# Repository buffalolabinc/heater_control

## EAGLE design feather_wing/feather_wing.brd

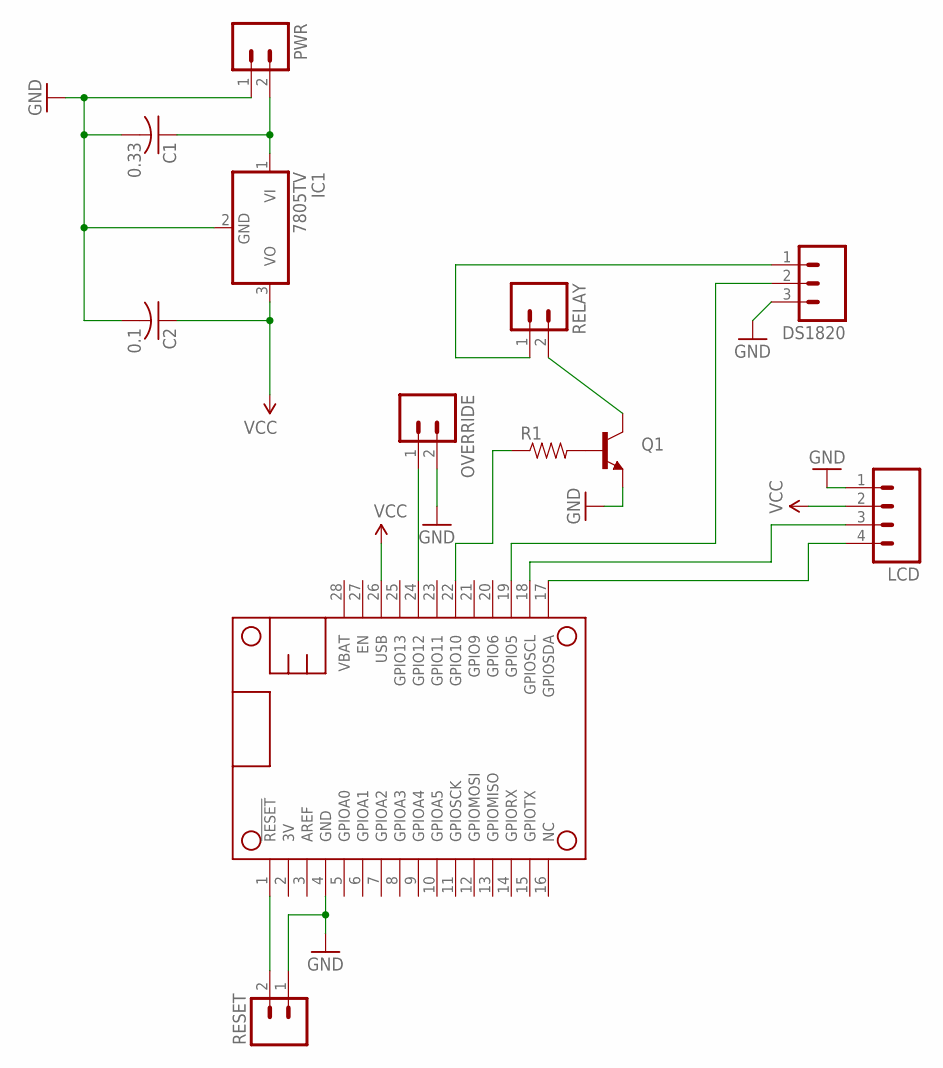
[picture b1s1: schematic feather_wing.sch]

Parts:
C1: 0.33; C025-025X050
C2: 0.1; C025-025X050
DS1820: M03SCREW; SCREWTERMINAL-3.5MM-3
IC1: 7805TV; TO220V
LCD: M04LOCK; 1X04_LOCK
MS1: FEATHERWING
OVERRIDE: M02PTH; 1X02
PWR: M023.5MM; SCREWTERMINAL-3.5MM-2
Q1: TRANSISTOR_NPNP2N2222A; TO-92
R1: RESISTORAXIAL-0.3; AXIAL-0.3
RELAY: M023.5MM; SCREWTERMINAL-3.5MM-2
RESET: M02PTH; 1X02

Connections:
GND: C1.2, C2.2, DS1820.3, IC1.2 (GND), LCD.1, MS1.4 (GND), OVERRIDE.2, PWR.1, Q1.3 (E), RESET.1
unnamed: C1.1, IC1.1 (VI), PWR.2
unnamed: DS1820.2, MS1.19 (GPIO5)
unnamed: MS1.24 (GPIO12), OVERRIDE.1
unnamed: Q1.1 (C), RELAY.2
unnamed: Q1.2 (B), R1.P$2 (2)
unnamed: MS1.22 (GPIO10), R1.P$1 (1)
unnamed: LCD.3, MS1.18 (GPIOSCL)
unnamed: LCD.4, MS1.17 (GPIOSDA)
unnamed: MS1.1 (!RESET), RESET.2
unnamed: DS1820.1, RELAY.1
VCC: C2.1, IC1.3 (VO), LCD.2, MS1.26 (USB)

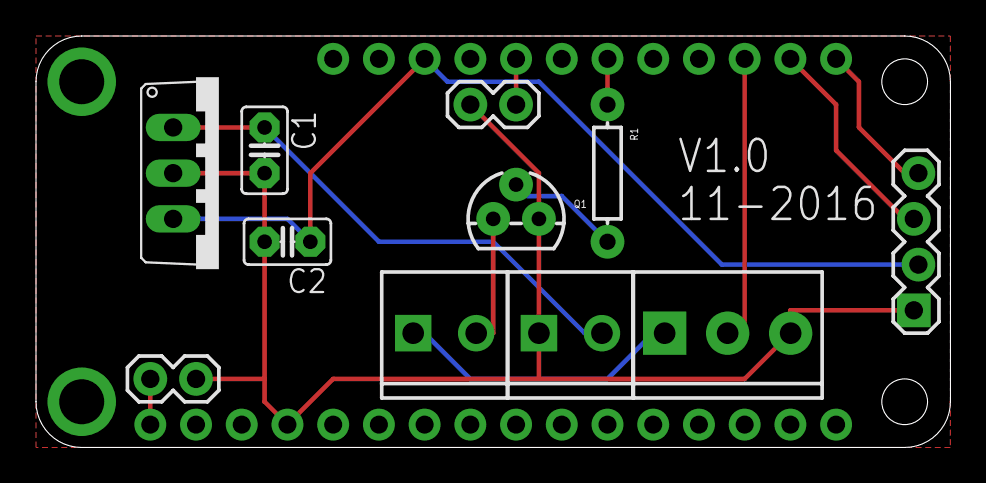
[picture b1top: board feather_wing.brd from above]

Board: 2 copper layers, 50.8 x 22.9 mm, 12 parts (0 on the bottom side), 12 nets.

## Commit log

2016-11-15 Initial check-in
    Thermostat sketch
2016-11-17 Change set points, no hang on Adafruit IO
    Changed set-points to 65 and 55.
    Will no longer block on failure to connect to Adafruit IO MQTT
2016-11-25 Take LCDDisplayTemp out of override ISR
2016-11-30 Re-do scheduler
    Change scheduler to avoid canceling timers on override.
    Also eliminate conflict between UTC and local time in CorrectDSTsettings
2016-12-01 improve scheduler and DST
2016-12-02 Daylight Savings, display, trace output changes
    Daylight savings is now done in UTC. Schedule operations are still
    local time.
    Added override indication to display.
    Removed some debug traces from temperature
    Changed MQTT trace text
2016-12-19 some debug prints
2016-12-26 Fix divide-by-zero when no sensors are attached.
2016-12-26 oops - meant to add a failsafe
    Heat won’t come on if no temp sensors are attached.
2016-12-29 Add override feed, change feed rate, debounce interrupt
    Added feed for the override state
    debounced override interrupt
    changed feed rate to be less than the MQTT keep alive interval of 5
    minutes.
2017-01-04 Add telnet settings
    MQTT settings now stored in EEPROM. Added telnet server for
    configuration
2017-01-04 move some includes to common.h
2017-01-04 Reinit MQTT after settings change
2017-01-05 Add scheduler values to telnet
    Add scheduler and setpoint values to telnet settings. Change override
    feed to setpoint feed
2017-01-05 comments
2017-01-05 fix problem with MQTT feeds
2017-01-06 Use edit buffer for changing settings
    Improve editing of settings with use of edit buffer. Prevents some
    setpoint settings from going live until save is executed
2017-01-08 Change setpoint settings to float
2017-01-15 WiFi retry on disconnect, settings updates
    WiFi now checks periodically for connection to AP and attempts
    reconnect.
    Can now update settings from serial port at startup
    Added WiFi SSID and Password to eeprom settings
2017-03-03 add backup of feather wing design
2017-03-09 Add version string to telnet output
    Starting at version 1.00
2017-03-09 Use DallasTemperature library
    TempSensors now uses higher-level DallasTemperature library. Sensors
    now set to 9-bit mode.
    Added tempList command to Settings
    Changed debounce in override ISR to 10ms
2017-03-09 Add comments
    links to onewire and dallas temperature libraries on github
2017-03-15 comments, minor changes
    Set temp update cycle to 5 seconds
    Set OTA hostname to match temp feed name
    Set OTA password to match Buffalo Lab password
2017-03-15 library links in comments
2017-03-23 change version number
    Changed to use DallasTemperature library. Update version number
2017-03-29 check for buffer overrun
    check for buffer overrun in telnet and serial
2018-02-01 Add reset to defaults command
    Added ‘defaults’ telnet command. Resets all settings to defaults.
2018-02-15 disable Wifi completely before re-connecting
2019-05-10 inital commit of graphing containers
2019-11-05 update mqtt frequency to 30 seconds
2019-11-05 add some debugging, increase debounce threshold
2019-11-05 add rssi to reporting
2019-11-05 should be Day End
2019-12-14 add some persistence
2021-10-28 clean up defs and remove defaults
2021-10-28 only check wifi every 10 minutes
2021-10-28 need this attribute for interrupt functions
2021-10-28 bump version to 1.12
2021-10-28 update comment about LCD library
2021-10-28 these are actually void methods
2021-10-28 add toggleOverride and status telnet commands
2021-10-28 use header from defaultSettings
2021-10-28 no need for AP mode
2021-10-28 bump version to 1.13-v20211028
2021-10-28 currentTemp is a float
2025-01-19 switch to using platformio
2025-01-19 set hostname for wifi/dhcp to match ota
2025-01-19 fix escape sequences
2025-01-19 do not persist wifi config
2025-01-19 remove commented lines

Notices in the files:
parts and their libraries:
SparkFun-Connectors: Licensing: Creative Commons ShareAlike 4.0 International - https://creativecommons.org/licenses/by-sa/4.0
